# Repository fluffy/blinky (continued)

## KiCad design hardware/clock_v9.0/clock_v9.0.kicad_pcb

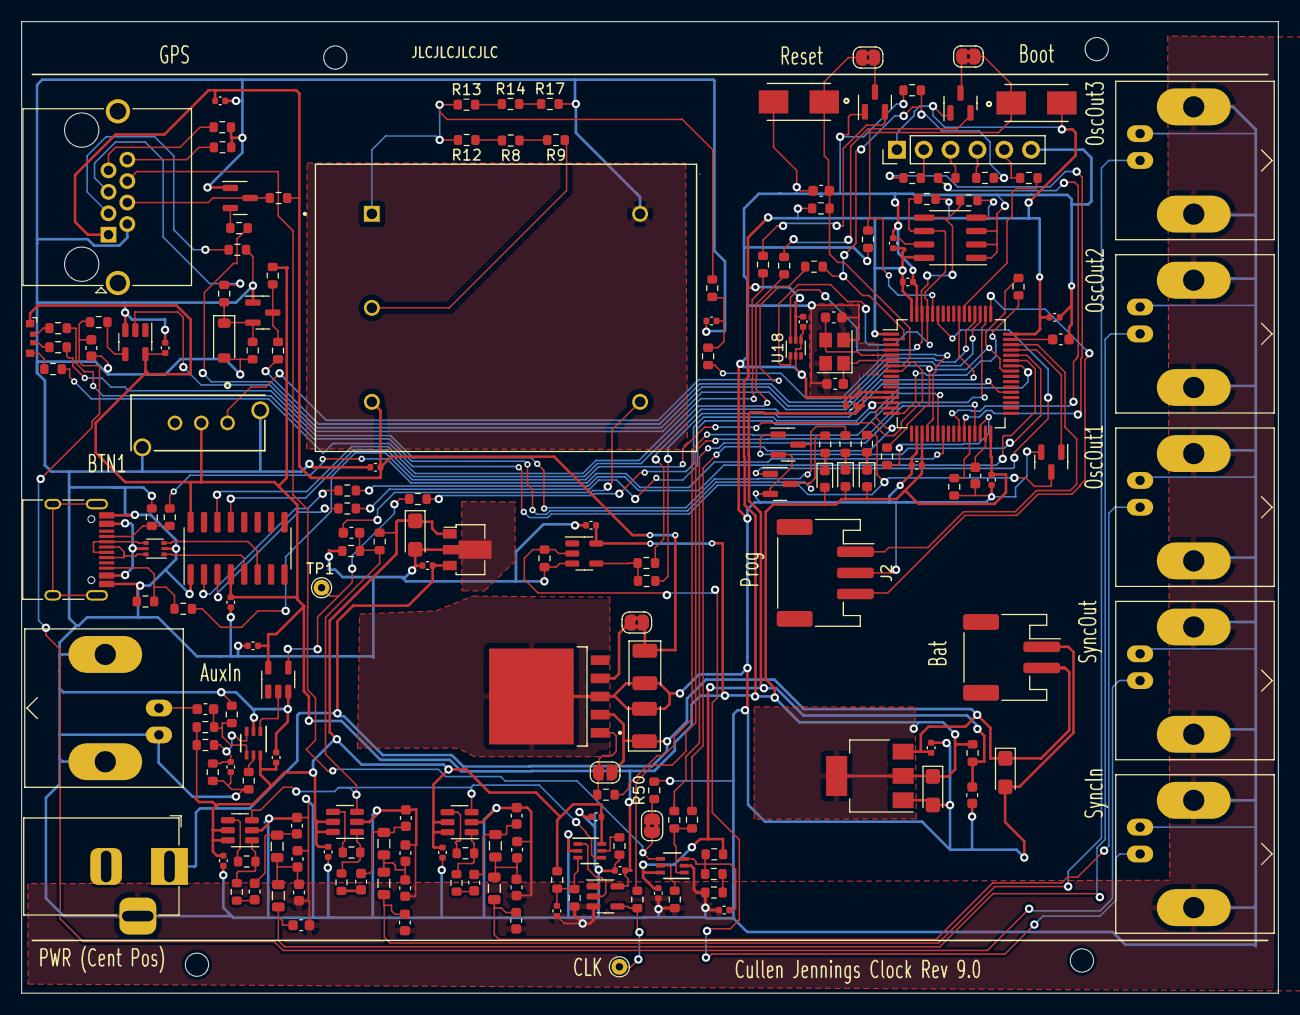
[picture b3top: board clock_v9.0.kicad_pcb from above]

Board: 2 copper layers, 119.0 x 92.0 mm, 194 parts (0 on the bottom side), 127 nets.

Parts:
C1, C2, C9, C10, C11, C17, C18, C25, C26, C30, C31, C32, C33, C36, C38, C39, C45, C46, C47, C48, C49, C50, C51, C52, C53, C55: 100n; C_0402_1005Metric
C3, C16, C21: 1n0; C_0603_1608Metric
C4: 47p; C_0603_1608Metric
C5, C7, C12, C14, C19, C23: 150p; C_0603_1608Metric
C6, C15, C22: 220p; C_0603_1608Metric
C8, C13, C20: 330p; C_0603_1608Metric
C24, C27, C37, C54: 100n; C_0603_1608Metric
C28, C29: 33p; C_0603_1608Metric
C34, C41, C43: 10u; CP_EIA-3216-18_Kemet-A
C35, C40: 2u2; C_0603_1608Metric
C42, C44: 33u; CP_EIA-3528-21_Kemet-B
D1: LED-R; LED_0603_1608Metric
D2: LED-G; LED_0603_1608Metric
D3: LED-Y; LED_0603_1608Metric
D4: 1N4148W; D_SOD-123
D5: LED_ABGR; LED_RGB_MHS110FRGBCT
FB1: 120Ω@100MHz; R_0603_1608Metric
H1, H2, H3, H4: M2; MountingHole_2.2mm_M2
J1: RJ45; RJ45_Amphenol_RJHSE5380
J2: Conn_01x03; JST_PH_S3B-PH-SM4-TB_1x03-1MP_P2.00mm_Horizontal
J3, J7, J9, J10, J11, J13: KH-BNC50-3511; BNC_Amphenol_B6252HB-NPP3G-50_Horizontal-CJ
J4: USB_C_Receptacle; USB_C_Receptacle_HRO_TYPE-C-31-M-12
J5: Conn_01x06_Pin; PinHeader_1x06_P2.54mm_Vertical
J8: Conn_01x02; JST_PH_S2B-PH-SM4-TB_1x02-1MP_P2.00mm_Horizontal
J14: DC-005I-5A-2.5; BarrelJack_Horizontal
JP1, JP2, JP3, JP4: SolderJumper_2_Bridged; SolderJumper-2_P1.3mm_Bridged2Bar_RoundedPad1.0x1.5mm
JP5: SolderJumper_2_Open; SolderJumper-2_P1.3mm_Open_RoundedPad1.0x1.5mm
L1, L2, L3, L4, L5, L6: 1uH; L_0805_2012Metric
Q1, Q9, Q10: 2N7002; SOT-23
Q2: S8550; SOT-23
Q3, Q4, Q5: S8050; SOT-23
R1, R15, R16, R29, R30, R31, R46, R47: 100R; R_0603_1608Metric
R2, R6, R10: 510R; R_0603_1608Metric
R3, R7, R11: 49R9; R_0603_1608Metric
R4: 200R; R_0603_1608Metric
R5, R19, R20, R22, R24, R39, R41, R42, R43, R44, R49, R51, R52, R53, R54, R55, R56, R57, R60, R61, R62, R63, R64, R65, R66, R67, R68, R69, R71, R72: 1K0; R_0603_1608Metric
R8, R25: 270R; R_0603_1608Metric
R9: 2R; R_0603_1608Metric
R12, R13, R58, R59: 1K5; R_0603_1608Metric
R14: 330R; R_0603_1608Metric
R17: 20R; R_0603_1608Metric
R18, R21, R45: 130K; R_0603_1608Metric
R23: 22K; R_0603_1608Metric
R26: 22R0; R_0603_1608Metric
R27, R28, R32, R33, R34, R36, R40, R48: 4K7; R_0603_1608Metric
R35: 2K2; R_0603_1608Metric
R37, R38: 5k1; R_0603_1608Metric
R50: 10K; R_0603_1608Metric
R70: 150R; R_0603_1608Metric
R73, R74: 47R; R_0603_1608Metric
S1, S3: 147873-2; SW_147873-2
SW1: LC1258OASP
TP1, TP10: TestPoint_THTPad_D1.5mm_Drill0.7mm
U1, U4, U5: ADA4807-1; SOT-23-6
U2, U3, U7, U17: SN74LVC1G14DBV; SOT-23-5
U6, U8, U16: TLV3603DCKR; SC70_DCK_TEX
U9: L78L05_SOT89; SOT-89-3
U10: STM32F405RGTx; LQFP-64_10x10mm_P0.5mm
U11: AMS1117-3.3; SOT-223-3_TabPin2
U12: BA50DD0WHFP-TR; DPAK172P1054X200-6N
U13: M24C02-RMN; SOIC-8_3.9x4.9mm_P1.27mm
U14: CH340C; SOIC-16_3.9x9.9mm_P1.27mm
U15: USBLC6-2P6; SOT-666
U18: TMP102xxDRL; SOT-563
Y1: AOCJY4A-10.000MHZ-SW; XTAL_AOCJY4A-10.000MHZ-SW
Y2: 16MHz; Crystal_SMD_3225-4Pin_3.2x2.5mm

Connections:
+3.3V: C9.1, C11.1, C31.1, C32.1, C36.1, C38.1, C41.1, C46.1, C47.2, C50.1, C53.1, C55.2, D1.2 (A), D2.2 (A), D3.2 (A), D5.1 (A), FB1.1, J5.1, Q2.1 (E), R27.1, R48.2, R58.1, R59.1, S3.2, SW1.2, U2.5 (VCC), U3.5 (VCC), U7.5 (VCC), U10.1 (VBAT), U10.19 (VDD), U10.32 (VDD), U10.48 (VDD), U10.64 (VDD), U11.2 (VO), U13.8 (VCC), U14.4 (V3), U14.16 (VCC), U17.5 (VCC), U18.5 (V+)
+3.3VA: C30.1, C37.2, C45.1, FB1.2, R22.1, U8.6 (VCC), U10.13 (VDDA)
+5V: C1.1, C18.1, C42.1, J1.1, JP4.2 (B), R53.2, Y1.3 (VDD)
+5VA: C2.1, C10.1, C17.1, C25.1, C34.1, C52.1, R15.1, R19.1, R43.1, R46.1, U1.5 (~DISABLE), U1.6 (V+), U4.5 (~DISABLE), U4.6 (V+), U5.5 (~DISABLE), U5.6 (V+), U6.6 (VCC), U9.1 (OUT), U16.6 (VCC)
+6V: C33.2, C39.2, C43.1, C44.1, J8.2, J14.1, JP5.2 (B), U9.3 (IN), U11.3 (VI), U12.2 (VCC)
/10Mhz2.5V: C24.2, R15.2, R16.1, U1.3 (+), U4.3 (+), U5.3 (+), U6.4 (-)
/AUD_IN: R71.2, U10.8 (PC0)
/AUX_MON_PPS: R62.2, U10.16 (PA2)
/BOOT0: JP2.1 (A), R28.1, S3.1, U10.60 (BOOT0)
/BOOT1: R32.2, U10.28 (PB2)
/BTN1: R40.2, R66.1, R72.2, U10.2 (PC13)
/DB3: R68.1, U10.54 (PD2)
/GPS_EN: J1.3, R1.1
/GPS_EXT_PPS: J1.6, JP3.2 (B), U8.4 (-)
/GPS_RX1: R49.1, U10.51 (PC10)
/GPS_RX1H: J1.4, Q5.3 (C), R53.1
/GPS_RX2H: J1.7, R33.2
/GPS_TX1: R52.1, U10.52 (PC11)
/GPS_TX1H: J1.5, R35.2
/GPS_TX2H: J1.8, R34.2
/HSE_IN: C28.1, U10.5 (PH0), Y2.3
/HSE_OUT: C29.1, U10.6 (PH1), Y2.1
/LED1: R69.2, U10.22 (PA6)
/LED2: R39.2, U10.23 (PA7)
/LED9: R67.1, U10.26 (PB0)
/LED10: R65.1, U10.27 (PB1)
/LEDMG: Q9.1 (G), U10.44 (PA11)
/LEDMR: Q1.1 (G), U10.45 (PA12)
/LEDMY: Q10.1 (G), U10.59 (PB7)
/MON_PPS: R54.2, U10.30 (PB11)
/NRST: C27.1, JP1.1 (A), R27.2, S1.1, U10.7 (NRST)
/OCXO_OUT: C24.1, Y1.4 (RF_OUTPUT)
/SCL: R59.2, U10.61 (PB8), U13.6 (SCL), U18.1 (SCL)
/SDA: R58.2, U10.62 (PB9), U13.5 (SDA), U18.6 (SDA)
/SWDCLK: J2.3, U10.49 (PA14)
/SWDIO: J2.1, U10.46 (PA13)
/USB_DTR: R41.2, U14.13 (~DTR)
/USB_RTS: R42.2, U14.14 (~RTS)
/USB_RX: R55.1, U10.42 (PA9)
/USB_TX: R51.2, U10.43 (PA10)
/Vadj: R12.2, R13.1, R23.2, Y1.1 (VC)
AUX_CLK: R56.1, TP1.1, U17.4
AUX_GPS_PPS: R61.2, U10.15 (PA1)
AUX_SYNC_IN: R64.1, U10.37 (PC6)
CLK: R57.1, TP10.1, U7.4
GND: C1.2, C2.2, C4.1, C5.2, C6.2, C7.1, C8.2, C9.2, C10.2, C11.2, C12.2, C13.2, C14.1, C15.2, C17.2, C18.2, C19.2, C20.2, C22.2, C23.1, C25.2, C26.2, C27.2, C28.2, C29.2, C30.2, C31.2, C32.2, C33.1, C34.2, C35.1, C36.2, C37.1, C38.2, C39.1, C40.1, C41.2, C42.2, C43.2, C44.2, C45.2, C46.2, C47.1, C48.2, C49.2, C50.2, C51.2, C52.2, C53.2, C55.1, D4.2 (A), J1.2, J2.2, J3.2 (Ext), J4.A1 (GND), J4.A12 (GND), J4.B1 (GND), J4.B12 (GND), J5.6, J7.2 (Ext), J8.1, J9.2 (Ext), J10.2 (Ext), J11.2 (Ext), J13.2 (Ext), J14.3, Q1.2 (S), Q3.1 (E), Q4.1 (E), Q5.1 (E), Q9.2 (S), Q10.2 (S), R1.2, R5.2, R16.2, R17.2, R18.2, R20.2, R21.2, R26.2, R28.2, R32.1, R33.1, R34.1, R36.1, R37.1, R38.1, R40.1, R44.2, R45.2, R47.2, R50.2, S1.2, SW1.4, SW1.5, U1.2 (V-), U2.3 (GND), U3.3 (GND), U4.2 (V-), U5.2 (V-), U6.2 (VEE), U7.3 (GND), U8.2 (VEE), U9.2 (GND), U10.12 (VSSA), U10.18 (VSS), U10.63 (VSS), U11.1 (GND), U12.3 (GND), U12.6 (GND), U13.1 (E0), U13.2 (E1), U13.3 (E2), U13.4 (VSS), U13.7 (~WC), U14.1 (GND), U15.2 (GND), U16.2 (VEE), U17.3 (GND), U18.2 (GND), U18.4 (ADD0), Y1.5 (GND), Y2.2, Y2.4
GPS_PPS: R60.1, U10.29 (PB10)
unnamed: C3.1, C5.1, L1.1
unnamed: C3.2, R3.2
unnamed: C6.1, C8.1, L1.2, L2.2
unnamed: C12.1, C16.1, L3.1
unnamed: C13.1, C15.1, L3.2, L4.2
unnamed: C16.2, R7.2
unnamed: C19.1, C21.1, L5.1
unnamed: C20.1, C22.1, L5.2, L6.2
unnamed: C21.2, R11.2
unnamed: C26.1, R23.1, R24.1
unnamed: D1.1 (K), R30.1
unnamed: D2.1 (K), R29.1
unnamed: D3.1 (K), R31.1
unnamed: D4.1 (K), Q4.2 (B), R35.1, R36.2
unnamed: D5.2 (BK), R74.1
unnamed: D5.3 (GK), R73.2
unnamed: D5.4 (RK), R70.2
unnamed: C23.2, J3.1 (In), L6.1
unnamed: J4.A5 (CC1), R38.2, R39.1
unnamed: J4.B5 (CC2), R37.2, R71.1
unnamed: J4.A6 (D+), J4.B6 (D+), U15.6 (I/O1)
unnamed: J4.A7 (D-), J4.B7 (D-), U15.4 (I/O2)
unnamed: J5.2, R65.2
unnamed: J5.3, R67.2
unnamed: J5.4, R66.2
unnamed: J5.5, R68.2
unnamed: C54.1, J7.1 (In)
unnamed: J9.1 (In), R5.1, U3.2
unnamed: C4.2, J10.1 (In), R4.2
unnamed: C14.2, J11.1 (In), L4.1
unnamed: C7.2, J13.1 (In), L2.1
unnamed: JP1.2 (B), Q3.3 (C)
unnamed: JP2.2 (B), Q2.3 (C)
unnamed: JP3.1 (A), R50.1
unnamed: JP4.1 (A), U12.4 (OUT)
unnamed: JP5.1 (A), R69.1, U12.1 (CTL)
unnamed: Q1.3 (D), R30.2, R70.1
unnamed: Q2.2 (B), R41.1
unnamed: Q3.2 (B), R42.1
unnamed: Q4.3 (C), R48.1, R52.2
unnamed: Q5.2 (B), R49.2
unnamed: Q9.3 (D), R29.2, R73.1
unnamed: Q10.3 (D), R31.2, R74.2
unnamed: R2.2, R3.1, U1.1
unnamed: R4.1, U2.4
unnamed: R6.2, R7.1, U4.1
unnamed: R8.1, R9.2
unnamed: R10.2, R11.1, U5.1
unnamed: R8.2, R12.1
unnamed: R13.2, R14.1
unnamed: R14.2, R17.1
unnamed: R25.2, R26.1
unnamed: R63.2, R64.2, U3.4
unnamed: R72.1, SW1.1
unnamed: R2.1, U1.4 (-)
unnamed: R6.1, U4.4 (-)
unnamed: R10.1, U5.4 (-)
unnamed: C49.1, R19.2, R20.1, U6.3 (+)
unnamed: R18.1, U6.5 (LE/HYS)
unnamed: U6.1 (OUT), U7.2
unnamed: C48.1, R22.2, R25.1, U8.3 (+)
unnamed: R21.1, U8.5 (LE/HYS)
unnamed: R60.2, R61.1, U8.1 (OUT)
unnamed: R56.2, U10.14 (PA0)
unnamed: R57.2, U10.50 (PA15)
unnamed: C35.2, U10.31 (VCAP_1)
unnamed: C40.2, U10.47 (VCAP_2)
unnamed: R55.2, U14.3 (RXD)
unnamed: R51.1, U14.2 (TXD)
unnamed: U14.5 (UD+), U15.1 (I/O1)
unnamed: U14.6 (UD-), U15.3 (I/O2)
unnamed: C51.1, R43.2, R44.1, U16.3 (+)
unnamed: C54.2, R46.2, R47.1, U16.4 (-)
unnamed: R45.1, U16.5 (LE/HYS)
unnamed: U16.1 (OUT), U17.2
unnamed: R9.1, Y1.2 (VREF)
OSC_ADJ: R24.2, U10.20 (PA4)
PPS_OUT: R54.1, R62.1, U2.2, U10.41 (PA8)
SYNC_IN: R63.1, U10.55 (PB3)
VBUS: J4.A4 (VBUS), J4.A9 (VBUS), J4.B4 (VBUS), J4.B9 (VBUS), U15.5 (VBUS)

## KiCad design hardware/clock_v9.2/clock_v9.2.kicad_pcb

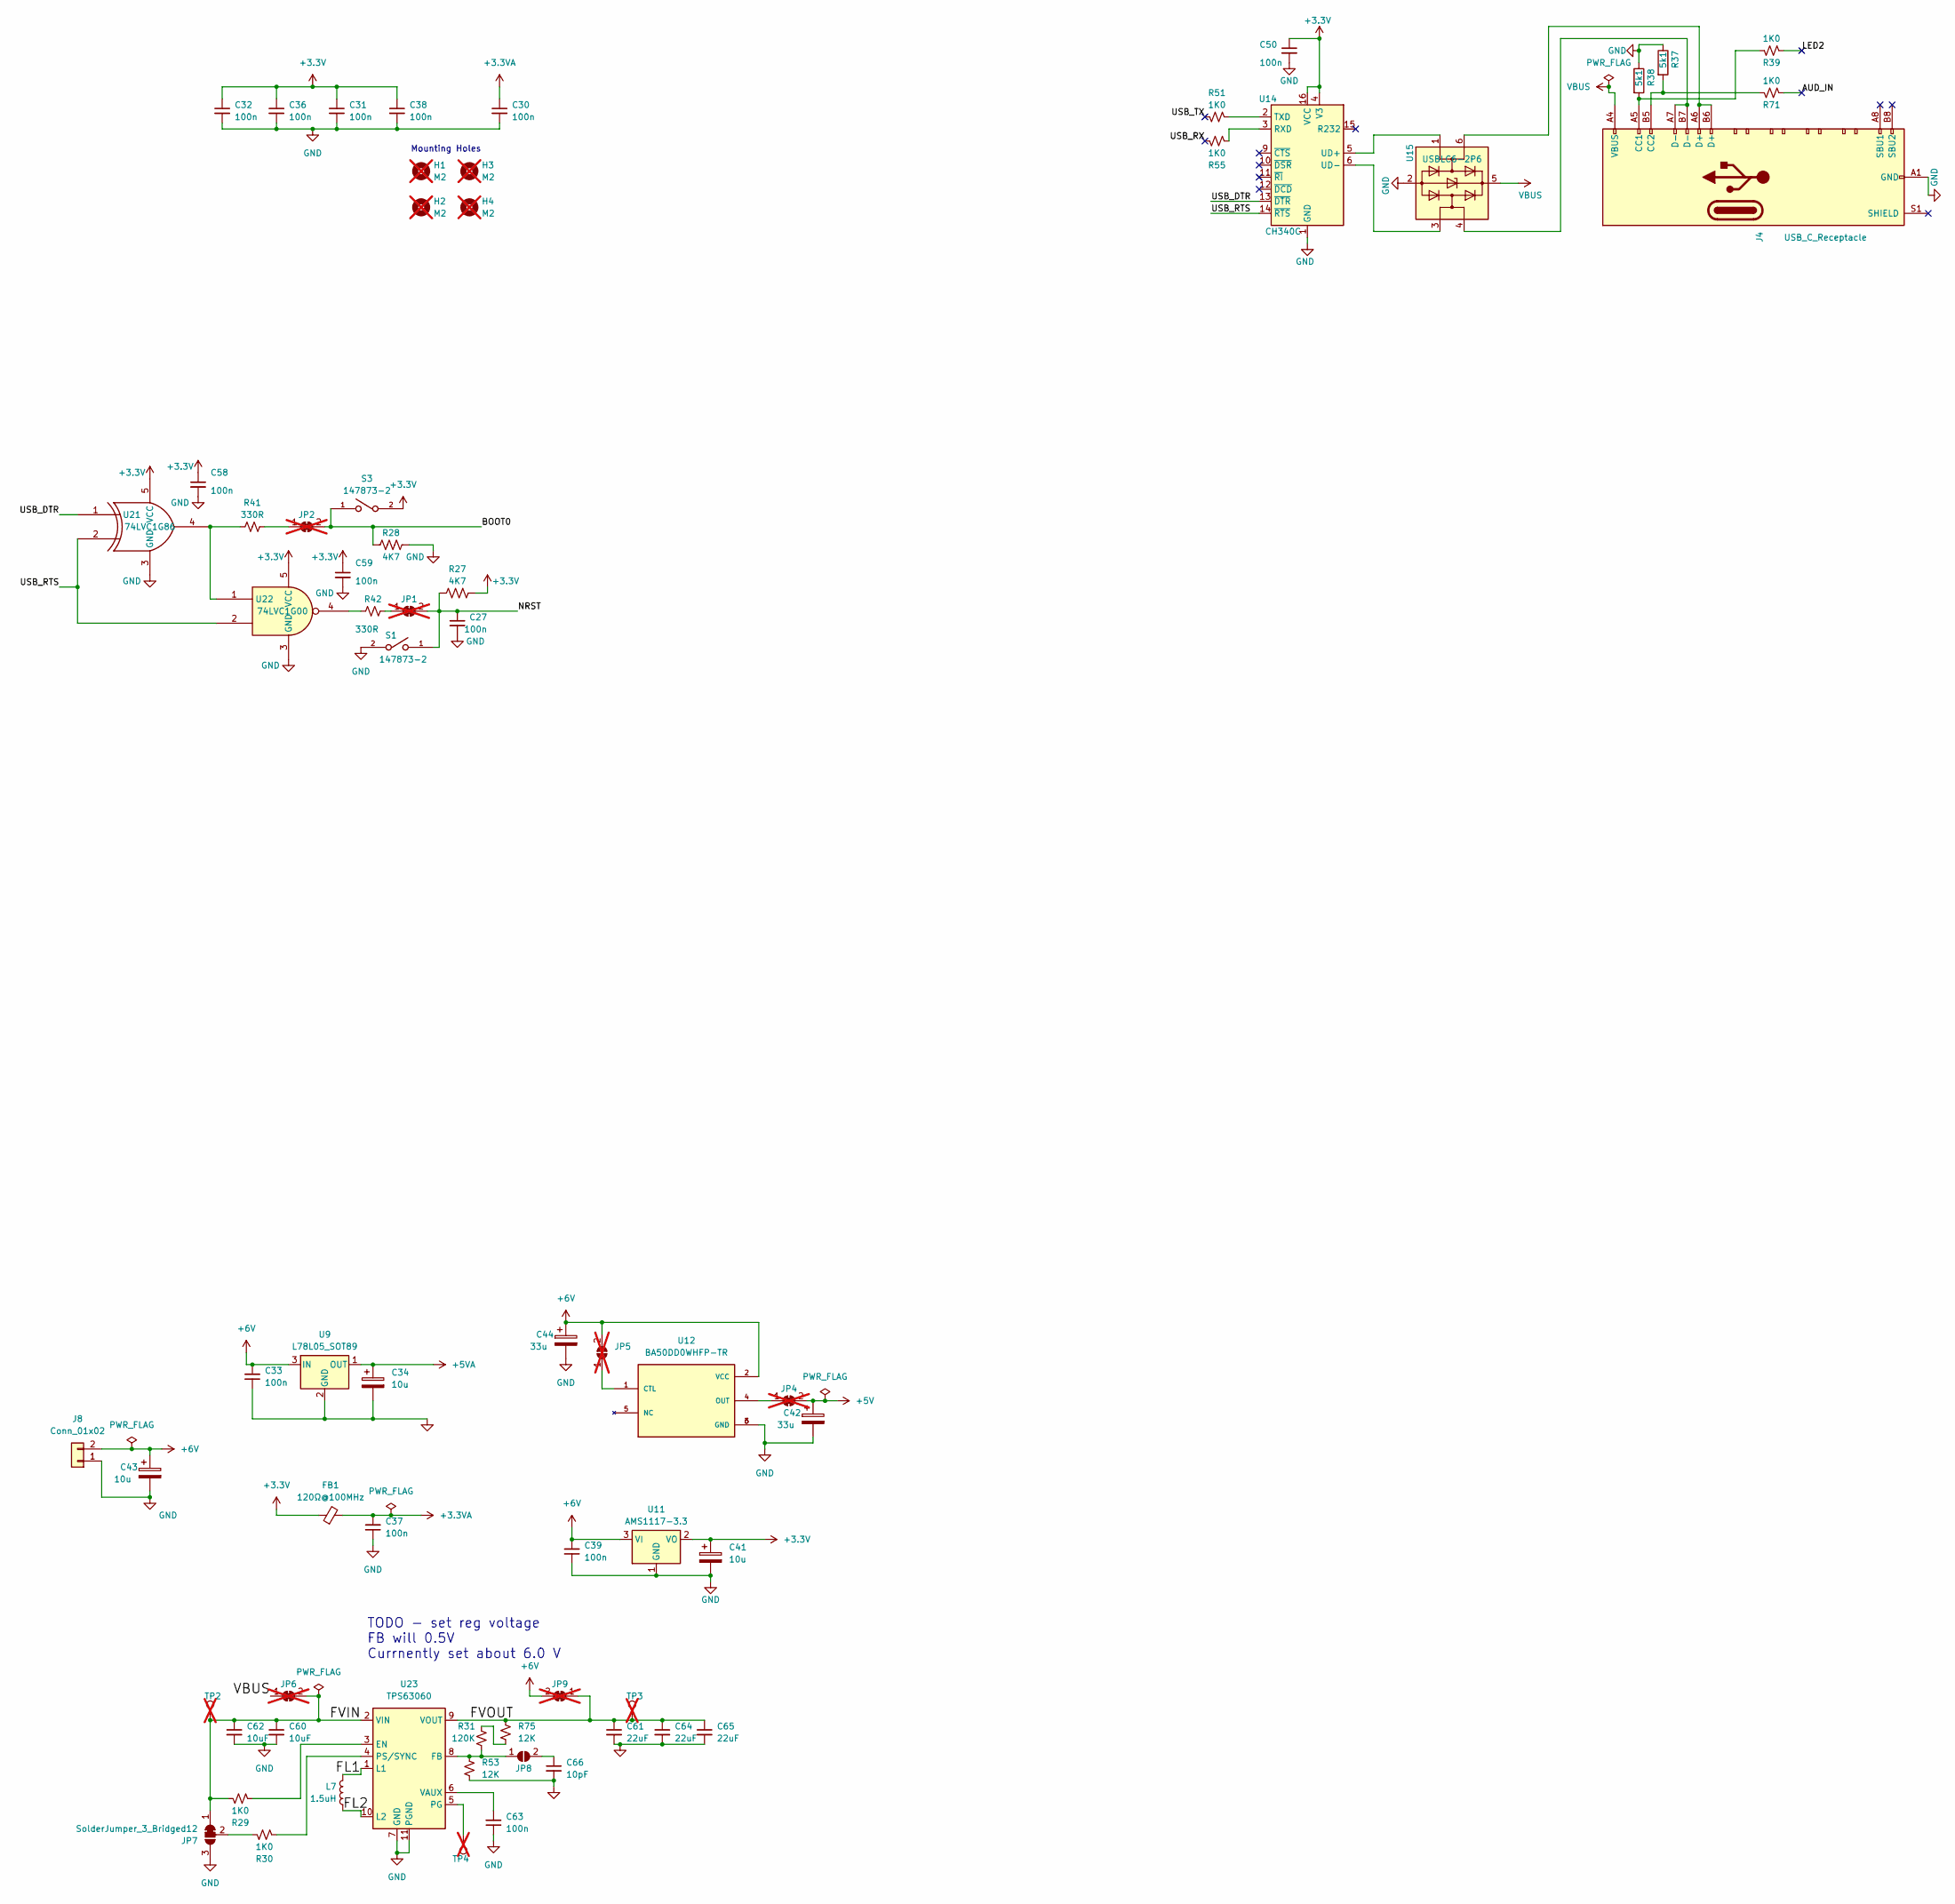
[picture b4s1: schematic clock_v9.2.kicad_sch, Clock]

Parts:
C27, C37, C63: 100n; C_0603_1608Metric; JLCPCB Part # C14663
C30, C31, C32, C33, C36, C38, C39, C50, C58, C59: 100n; C_0402_1005Metric; JLCPCB Part # C307331
C34, C41, C43: 10u; CP_EIA-3216-18_Kemet-A; JLCPCB Part # C7171
C42, C44: 33u; CP_EIA-3528-21_Kemet-B; JLCPCB Part # C128342
C60, C62: 10uF; C_0603_1608Metric; JLCPCB Part # C96446
C61, C64, C65: 22uF; C_0805_2012Metric; JLCPCB Part # C45783
C66: 10pF; C_0603_1608Metric; JLCPCB Part # C1634
FB1: 120Ω@100MHz; R_0603_1608Metric; JLCPCB Part # C127301
H1, H2, H3, H4: M2; MountingHole_2.2mm_M2; not fitted
J4: USB_C_Receptacle; USB_C_Receptacle_HRO_TYPE-C-31-M-12; JLCPCB Part # C165948
J8: Conn_01x02; JST_PH_S2B-PH-SM4-TB_1x02-1MP_P2.00mm_Horizontal; JLCPCB Part # C295747
JP1, JP2, JP4, JP6, JP9: SolderJumper_2_Bridged; SolderJumper-2_P1.3mm_Bridged2Bar_RoundedPad1.0x1.5mm; not fitted
JP5: SolderJumper_2_Open; SolderJumper-2_P1.3mm_Bridged_RoundedPad1.0x1.5mm; not fitted
JP7: SolderJumper_3_Bridged12; SolderJumper-3_P1.3mm_Bridged2Bar12_RoundedPad1.0x1.5mm
JP8: SolderJumper_2_Open; SolderJumper-2_P1.3mm_Open_RoundedPad1.0x1.5mm
L7: 1.5uH; L_Coilcraft_XAL4020-XXX; MPN XFL4020-152MEC; JLCPCB Part # C3033018
R27, R28: 4K7; R_0603_1608Metric; JLCPCB Part # C23162
R29, R30, R39, R51, R55, R71: 1K0; R_0603_1608Metric; JLCPCB Part # C21190
R31: 120K; R_0603_1608Metric
R37, R38: 5k1; R_0603_1608Metric; JLCPCB Part # C23186
R41, R42: 330R; R_0603_1608Metric; JLCPCB Part # C23138
R53, R75: 12K; R_0603_1608Metric; JLCPCB Part # C22790
S1, S3: 147873-2; SW_147873-2; JLCPCB Part # C266189
TP2, TP3, TP4: TestPoint_THTPad_D1.5mm_Drill0.7mm; not fitted
U9: L78L05_SOT89; SOT-89-3; JLCPCB Rotation Offset 180
U11: AMS1117-3.3; SOT-223-3_TabPin2; JLCPCB Rotation Offset 180
U12: BA50DD0WHFP-TR; DPAK172P1054X200-6N; PARTREV 003; JLCPCB Position Offset -1.5,0
U14: CH340C; SOIC-16_3.9x9.9mm_P1.27mm; JLCPCB Part # C84681
U15: USBLC6-2P6; SOT-666; JLCPCB Part # C2827693
U21: 74LVC1G86; SOT-23-5; JLCPCB Part # C402161
U22: 74LVC1G00; SOT-23-5; JLCPCB Part # C7826
U23: TPS63060; Texas_S-PWSON-N10_ThermalVias; JLCPCB Part # C48567

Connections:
+3.3V: C31.1, C32.1, C36.1, C38.1, C41.1, C50.1, C58.1, C59.1, FB1.1, R27.1, S3.2, U11.2 (VO), U14.4 (V3), U14.16 (VCC), U21.5 (VCC), U22.5 (VCC)
+3.3VA: C30.1, C37.2, FB1.2
+5V: C42.1, JP4.2 (B)
+5VA: C34.1, U9.1 (OUT)
+6V: C33.2, C39.2, C43.1, C44.1, J8.2, JP5.2 (B), JP9.2 (B), U9.3 (IN), U11.3 (VI), U12.2 (VCC)
/AUD_IN: R71.2
/BOOT0: JP2.2 (B), R28.1, S3.1
/FL1: L7.1, U23.1 (L1)
/FL2: L7.2, U23.10 (L2)
/FVIN: C60.1, C62.1, JP6.2 (B), JP7.1 (A), R29.1, TP2.1, U23.2 (VIN)
/FVOUT: C61.1, C64.1, C65.1, JP9.1 (A), R75.1, TP3.1, U23.9 (VOUT)
/LED2: R39.2
/NRST: C27.1, JP1.2 (B), R27.2, S1.1
/USB_DTR: U14.13 (~DTR), U21.1
/USB_RTS: U14.14 (~RTS), U21.2, U22.2
/USB_RX: R55.1
/USB_TX: R51.2
GND: C27.2, C30.2, C31.2, C32.2, C33.1, C34.2, C36.2, C37.1, C38.2, C39.1, C41.2, C42.2, C43.2, C44.2, C50.2, C58.2, C59.2, C60.2, C61.2, C62.2, C63.1, C64.2, C65.2, C66.2, J4.A1 (GND), J4.A12 (GND), J4.B1 (GND), J4.B12 (GND), J8.1, JP7.3 (B), R28.2, R37.1, R38.1, R53.2, S1.2, U9.2 (GND), U11.1 (GND), U12.3 (GND), U12.6 (GND), U14.1 (GND), U15.2 (GND), U21.3 (GND), U22.3 (GND), U23.7 (GND), U23.11 (PGND)
unnamed: J4.A5 (CC1), R38.2, R39.1
unnamed: J4.B5 (CC2), R37.2, R71.1
unnamed: J4.A6 (D+), J4.B6 (D+), U15.6 (I/O1)
unnamed: J4.A7 (D-), J4.B7 (D-), U15.4 (I/O2)
unnamed: JP1.1 (A), R42.1
unnamed: JP2.1 (A), R41.2
unnamed: JP4.1 (A), U12.4 (OUT)
unnamed: JP5.1 (A), U12.1 (CTL)
unnamed: JP7.2 (C), R30.1
unnamed: JP8.1 (A), R31.2, R53.1, U23.8 (FB)
unnamed: C66.1, JP8.2 (B)
unnamed: R31.1, R75.2
unnamed: R41.1, U21.4, U22.1
unnamed: R42.2, U22.4
unnamed: R55.2, U14.3 (RXD)
unnamed: R51.1, U14.2 (TXD)
unnamed: U14.5 (UD+), U15.1 (I/O1)
unnamed: U14.6 (UD-), U15.3 (I/O2)
unnamed: R29.2, U23.3 (EN)
unnamed: TP4.1, U23.5 (PG)
unnamed: R30.2, U23.4 (PS/SYNC)
unnamed: C63.2, U23.6 (VAUX)
VBUS: J4.A4 (VBUS), J4.A9 (VBUS), J4.B4 (VBUS), J4.B9 (VBUS), JP6.1 (A), U15.5 (VBUS)

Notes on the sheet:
Mounting Holes
TODO - set reg voltage FB will 0.5V Currnently set about 6.0 V

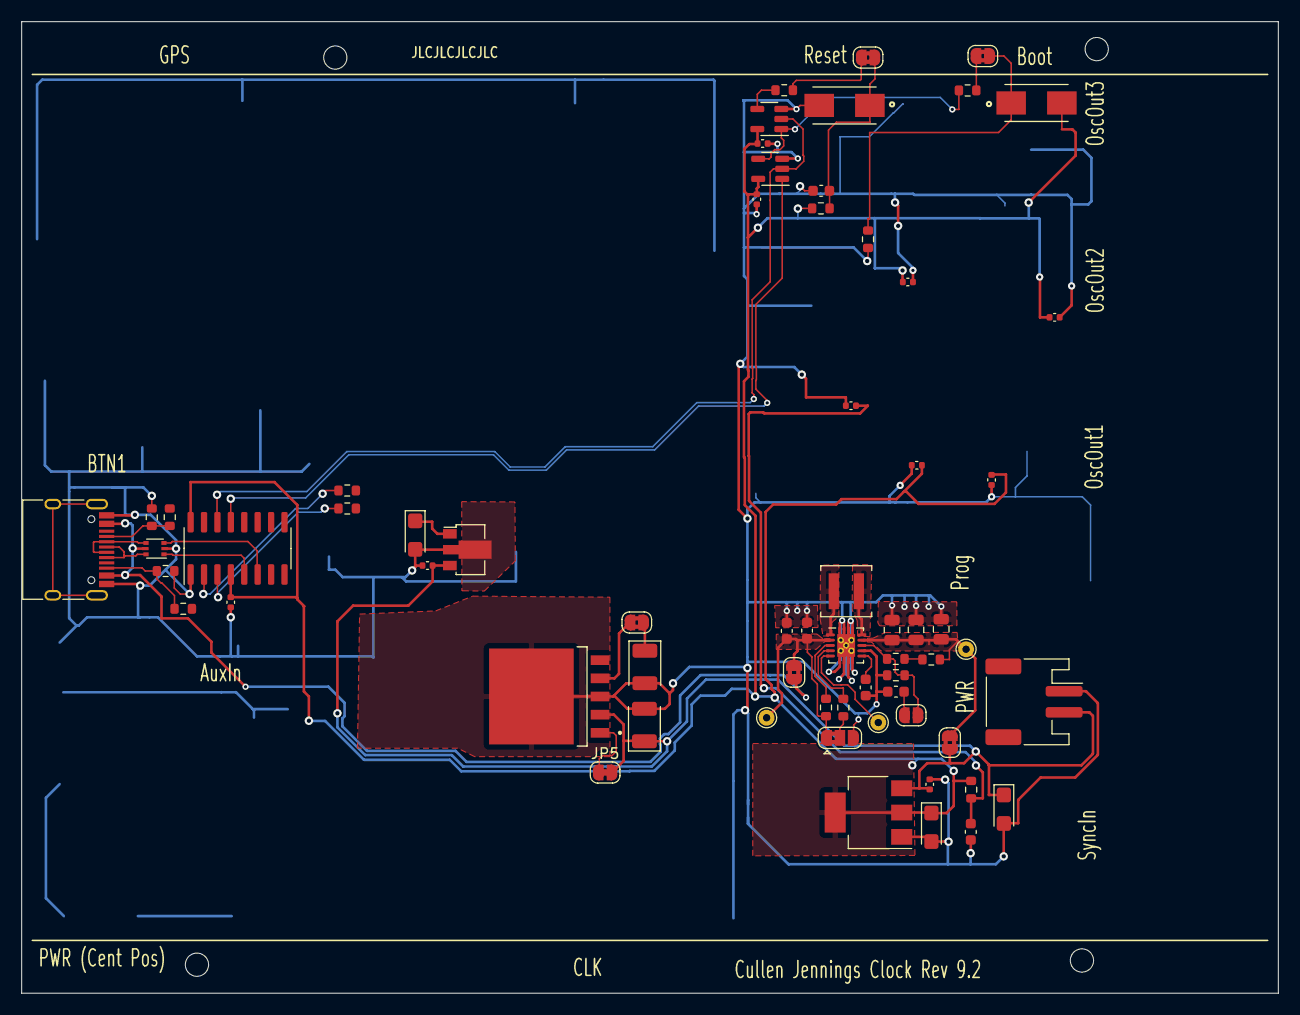
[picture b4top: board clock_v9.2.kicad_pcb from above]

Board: 2 copper layers, 119.0 x 92.0 mm, 68 parts (0 on the bottom side), 37 nets.
